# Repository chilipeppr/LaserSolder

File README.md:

LaserSolder
===========

The laser solderer widget for ChiliPeppr that uses an Arduino to control a laser with an infrared heat sensor and a PID to ensure accurate soldering.

ChiliPeppr Widget
-----------

The widget lets you set at which Z height the laser will turn on. The laser is toggled from a normal Arduino. The command "laser-on" or "laser-off" is sent to the Arduino to toggle. You must also pick which port the Arduino is on. The Arduino also reports back every 500ms what the temperature of the Melexis infrared heat sensor readings are as a JSON string in the format {"a":27.54, "o":31.34} where "a" is the ambient temperature and "o" is the object's temperature in degrees Celsius. You can also toggle the laser manually.

When the laser is on the widget goes red to indicate the state. You can always manually turn the laser off to override the auto-toggling based on the Z axis position.

Arduino Code
----------

Just use a standard Arduino and upload the code contained in this repository. Modify as you like. You'll be running your Arduino on the same computer as your CNC machine so you can bind to both the serial port of your CNC controller like a TinyG as well as bind to your Arduino via its serial port.

The Arduino controls a laser by toggling PIN 12 on and off. You need
to connect a solid state relay, regular relay, or toggle a TTL signal
on a bench power supply. Or you can use something like a FlexMod P3
to toggle the laser on/off.

The laser used is a 3W 445nm Blue Diode laser in a standard 9mm casing
with a heatsink. You can find the laser at https://sites.google.com/site/dtrlpf/home/diodes/9mm-445nm

The Melexis MLX90614 is used for infrared temperature sensing. You
should get the 5 degree FOV version which is around $48. The link to this sensor is http://www.digikey.com/product-detail/en/MLX90614ESF-BCI-000-TU/MLX90614ESF-BCI-000-TU-ND/2666249

Eagle Schematics
----------

The Eagle design is in the eagle folder of this repository. It's simply a breakout board for the Melexis MLX90614 so you can connect it to your Arduino. It has two LEDs to indicate laser on/off status and power to the Melexis. There is a cutout on the board so you can bolt it to the design of the holder that is described below.

Freecad Design
----------

The design of the holder for the laser, Melexis MLX90614, the breakout board, and USB Microscope is in the freecad folder in this repo. Freecad is a great tool for basic CAD design. The CAD design was exported to DXF's and then brought into CamBam to generate the acrylic milling operations. The acrylic was then super glued or bolted together. Several M3 an M4 taps were created in the acrylic to enable bolting.

The back holder mounts to the standard Shapeoko mounts for a spindle so you can adjust the height of the laser holder on your Shapeoko.

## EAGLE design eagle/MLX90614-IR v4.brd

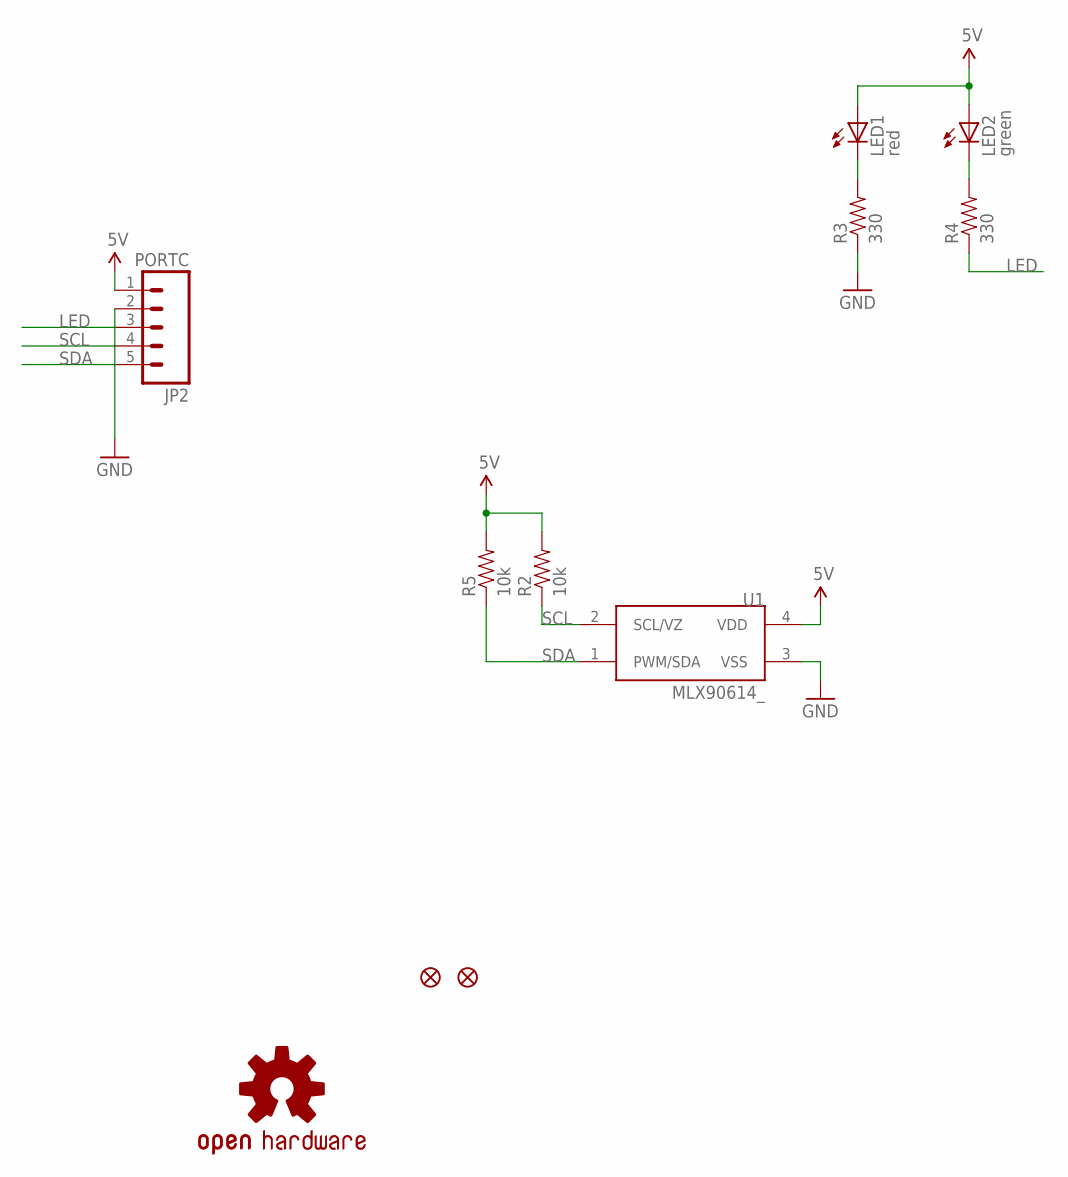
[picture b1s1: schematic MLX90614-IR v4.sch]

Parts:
JP2: PORTC; 1X05
JP3, JP5: FIDUCIAL1X2.5; FIDUCIAL-1X2.5
LED1: red; LED-0603
LED2: green; LED-0603
R2, R5: 10k; 0402-RES
R3, R4: 330; 0402-RES
U1: MLX90614_; TO-39
U$1: OSHW-LOGOS; OSHW-LOGO-S

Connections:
5V: JP2.1, LED1.A, LED2.A, R2.2, R5.2, U1.4 (VDD)
GND: JP2.2, R3.1, U1.3 (VSS)
LED: JP2.3, R4.1
unnamed: LED1.C, R3.2
unnamed: LED2.C, R4.2
SCL: JP2.4, R2.1, U1.2 (SCL/VZ)
SDA: JP2.5, R5.1, U1.1 (PWM/SDA)

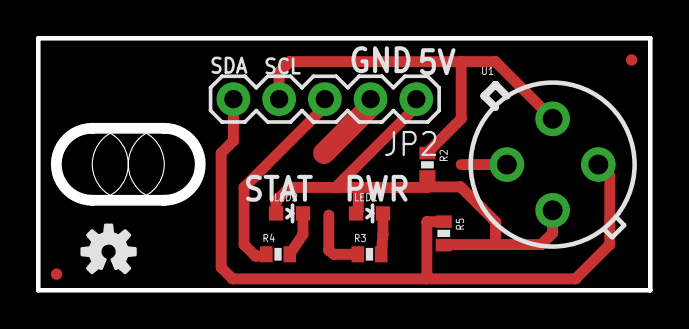
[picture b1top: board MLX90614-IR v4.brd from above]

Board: 2 copper layers, 33.7 x 13.7 mm, 11 parts (0 on the bottom side), 7 nets.

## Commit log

2014-09-21 :lollipop: Added .gitattributes & .gitignore files
2014-09-21 First check in
2014-09-21 Screenshot
2014-09-21 More screenshots
2014-09-21 Eagle
2014-09-21 arduino

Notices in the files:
parts and their libraries:
SparkFun-Connectors: Licensing: Creative Commons ShareAlike 4.0 International - https://creativecommons.org/licenses/by-sa/4.0
